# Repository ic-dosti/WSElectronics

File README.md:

# About authors:
- Esmagambet Doshan
- Tumanov Artyom

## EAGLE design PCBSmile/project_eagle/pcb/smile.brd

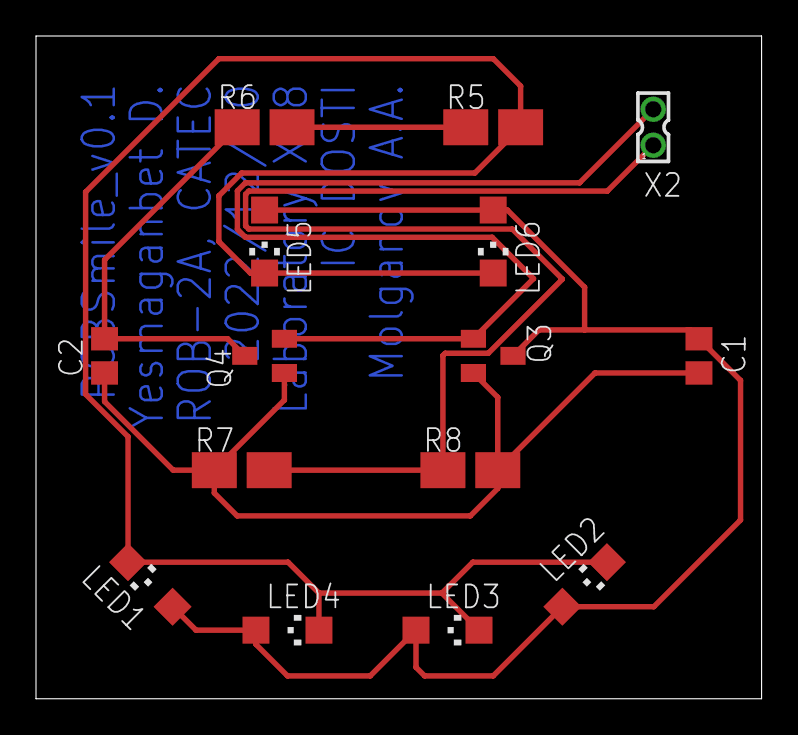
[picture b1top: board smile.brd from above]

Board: 2 copper layers, 40.3 x 36.8 mm, 15 parts (0 on the bottom side), 6 nets.

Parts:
C1, C2: 100p; C0805
LED1, LED2, LED3, LED4, LED5, LED6: CHIPLED_1206
Q3, Q4: PNP; SOT23
R5, R6, R7, R8: SMK
X2: 332-02

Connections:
GND: C1.2, C2.1, Q3.2, Q4.1, R7.2, R8.1
unnamed: C1.1, LED1.A, LED2.A, LED3.A, LED4.A, LED5.A, LED6.A, Q3.3
unnamed: Q3.1, Q4.2, X2.2
unnamed: R5.2, R6.1, R7.1, R8.2, X2.1
unnamed: LED1.C, LED2.C, LED3.C, LED4.C, LED5.C, LED6.C, R5.1
unnamed: C2.2, Q4.3, R6.2

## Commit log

2022-12-03 20220312_1102
2022-12-03 20220312_110250
2022-12-03 20221203_110311
2022-12-03 20221203_110404
2022-12-09 20221209_081340
2022-12-09 20221209_081450
2022-12-10 first project commit
2022-12-10 add OpAmpDevBoard folders
2022-12-16 add smile scheme
2023-02-14 20230214_084256
2023-03-16 Second
2023-03-18 Add Music_box, Sound_amplifier, FM_Radio
2023-03-18 Changes in README
2023-03-18 Some Changes in README
2023-03-18 20230318_174200
2023-03-27 20230327_130600
2023-05-07 new structure
2023-06-30 20230630_1928
2023-08-04 20230804_0943
2023-08-12 20230812_1329
2023-09-21 20230921_1612
2023-11-09 20231109_1634
2024-01-22 20240122_0919
2024-01-22 20240122_091902
2024-01-22 20240122_0931
2024-01-26 20240126_1629
2024-01-27 20240127_0832
2024-02-09 20240209_1101
2024-03-12 20240312_1123
2024-03-16 20240316_1637
2024-03-20 20240320_1330
2024-03-22 20240322_2133
2024-03-22 20240322_2136
2024-04-12 20240412_1645
2024-08-05 20240805_1823
